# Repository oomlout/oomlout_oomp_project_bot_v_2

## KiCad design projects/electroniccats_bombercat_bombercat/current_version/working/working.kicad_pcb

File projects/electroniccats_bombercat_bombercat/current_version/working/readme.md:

# bombercat
 
## summary 
* id: electroniccats_bombercat_bombercat
* user: electroniccats
* name: bombercat
* board: bombercat
* repo: https://github.com/ElectronicCats/BomberCat
* src_file_repo_kicad_pcb: hardware/BomberCat.kicad_pcb
* src_file_repo_kicad_pcb_link: https://github.com/ElectronicCats/BomberCat/tree/main/hardware/BomberCat.kicad_pcb
* src_file_repo_kicad_sch: hardware/BomberCat.kicad_sch
* src_file_repo_kicad_sch_link: https://github.com/ElectronicCats/BomberCat/tree/main/hardware/BomberCat.kicad_sch

* src_file_repo_sch: 
* src_file_repo_sch_link: https://github.com/ElectronicCats/BomberCat/tree/main/
* full details link: https://github.com/oomlout/oomlout_oomp_project_bot_v_2/tree/main/projects/electroniccats_bombercat_bombercat/current_version/working

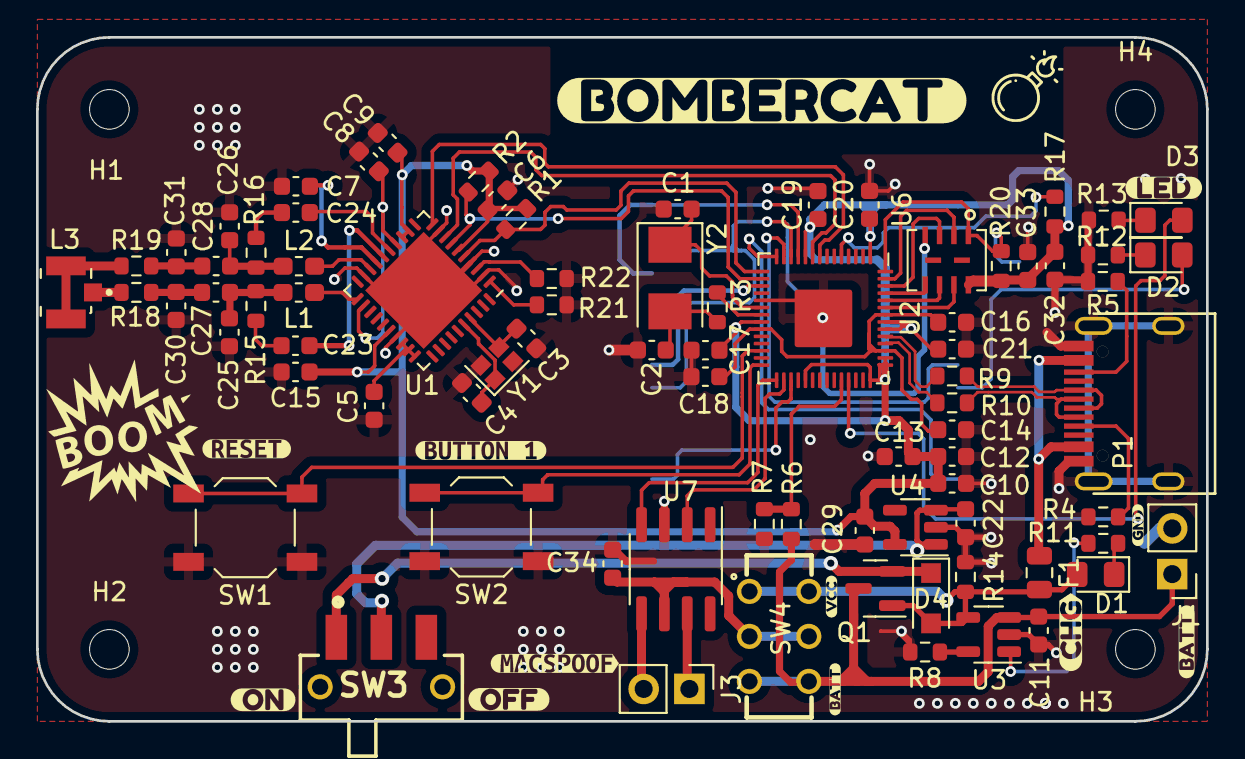
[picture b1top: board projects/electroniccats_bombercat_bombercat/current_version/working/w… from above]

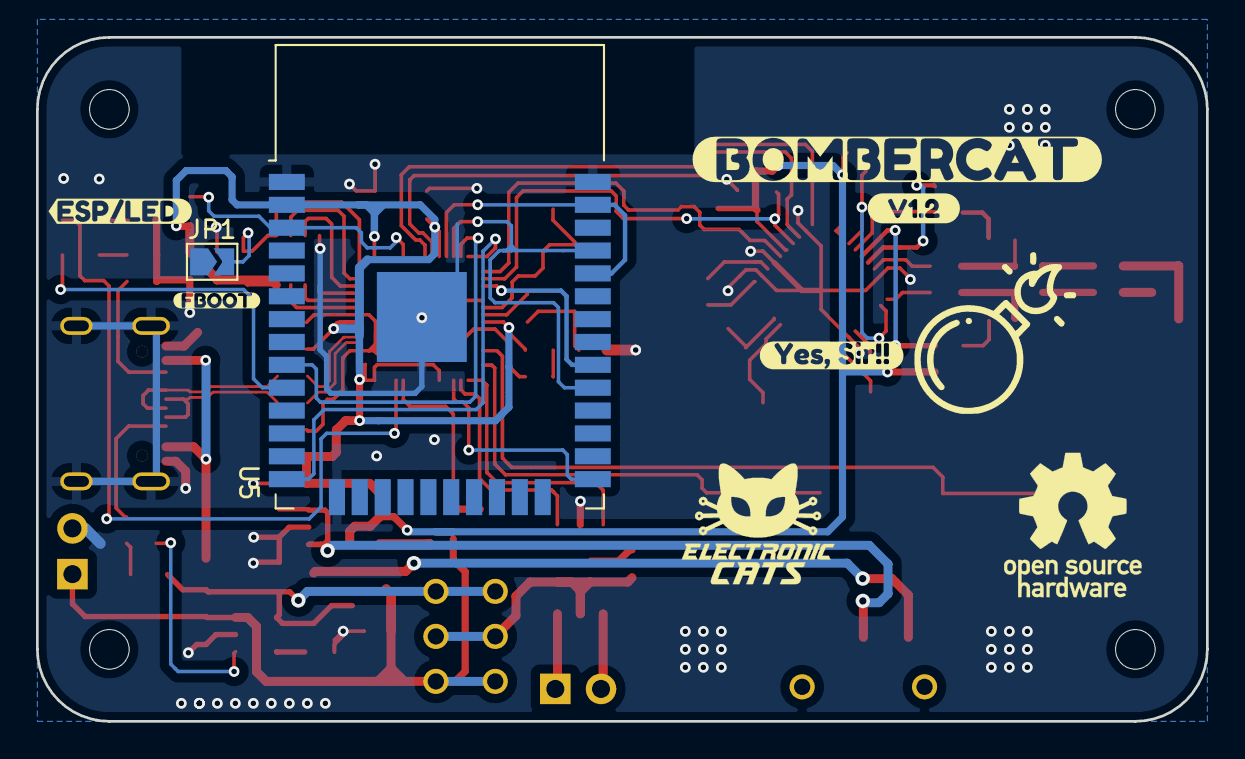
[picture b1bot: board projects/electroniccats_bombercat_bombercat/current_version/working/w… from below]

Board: 2 copper layers, 65.0 x 38.0 mm, 103 parts (7 on the bottom side), 68 nets.

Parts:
C1, C2: 27pF; C_0603_1608Metric
C3, C4: 10pF; C_0603_1608Metric
C5, C6, C8, C10, C14: 1uF; C_0603_1608Metric
C7, C9, C12, C13, C15, C16, C17, C18, C19, C20, C21, C32, C33: 100nF; C_0603_1608Metric
C11, C22, C29: 10uF; C_0603_1608Metric
C23, C24: 1nF/16V; C_0603_1608Metric
C25, C26: 680pF; C_0603_1608Metric
C27, C28: 100pF/50V; C_0603_1608Metric
C30, C31: 120pF; C_0603_1608Metric
C34: 10uf; C_0603_1608Metric
D1, D2, D3: LED; LED_0805_2012Metric_Pad1.15x1.40mm_HandSolder
D4: MBR120; D_SOD-123F
F1: 0.5A; Fuse_0805_2012Metric
H1, H2, H3, H4: MountingHole; MountingHole_2.2mm_M2
J1: Battery; PinHeader_1x02_P2.54mm_Vertical
J3: MAGSPOOF; PinHeader_1x02_P2.54mm_Vertical
JP1: BOOT; SolderJumper-2_P1.3mm_Open_TrianglePad1.0x1.5mm
L1, L2: 160nH; L_0603_1608Metric_Pad1.05x0.95mm_HandSolder
L3: L; MOLEX_1661
P1: USB_C_Plug_USB2.0; C393939
Q1: DMG3415U-7; SOT-23
R1, R2, R17, R20: 10K; R_0603_1608Metric
R3, R11, R12, R13: 1K; R_0603_1608Metric
R4, R5: 5k1; R_0603_1608Metric
R6, R7, R14, R21, R22: 100K; R_0603_1608Metric
R8: 2K; R_0603_1608Metric
R9, R10: 27; R_0603_1608Metric
R15, R16: 2k2; R_0603_1608Metric
R18, R19: 3.24R; R_0603_1608Metric
SW1: RESET; SW_SPST_TL3342
SW2: GPIO; SW_SPST_TL3342
SW3: ON; JS102011SAQN
SW4: SOURCE MAG; JS202011CQN
U1: PN7150B0HN_C11002E-PN7150B0HN_C11002E; QFN-40-1EP_6x6mm_P0.5mm_EP4.6x4.6mm
U2: RP2040; RP2040-QFN-56
U3: MCP73831-3-OT; SOT-23-5
U4: AP2112K-3.3; SOT-23-5
U5: ESP32-WROOM-32D; ESP32-WROOM-32
U6: W25Q16JV; W25Q16JVUUIQ
U7: TC4424; SOIC-8_3.9x4.9mm_P1.27mm
Y1: 27.12Mhz; Crystal_SMD_2016-4Pin_2.0x1.6mm
Y2: 12Mhz; Crystal_SMD_5032-2Pin_5.0x3.2mm
kibuzzard-62CC5B78, kibuzzard-62CC5B78#2: G***; kibuzzard-62CC5B78
kibuzzard-62CC5BEF: G***; kibuzzard-62CC5BEF
kibuzzard-62CC9A49: G***; kibuzzard-62CC9A49
kibuzzard-62CC57AB: G***; kibuzzard-62CC57AB
kibuzzard-62CC595D: G***; kibuzzard-62CC595D
kibuzzard-62CC5774: G***; kibuzzard-62CC5774
kibuzzard-62CC5787: G***; kibuzzard-62CC5787
kibuzzard-62CC5892: G***; kibuzzard-62CC5892
kibuzzard-62E1B2BF: G***; kibuzzard-62E1B2BF
kibuzzard-62E1B24A: G***; kibuzzard-62E1B24A
kibuzzard-62E1B288: G***; kibuzzard-62E1B288
kibuzzard-62E1B296: G***; kibuzzard-62E1B296
kibuzzard-62E41048: G***; kibuzzard-62E41048
kibuzzard-62EEB073: G***; kibuzzard-62EEB073
kibuzzard-62EEB113: G***; kibuzzard-62EEB113
kibuzzard-64382690: G***; kibuzzard-64382690

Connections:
+1V2: C14.1, C16.1, C18.1, U2.23 (DVDD), U2.45 (VREG_VOUT), U2.50 (DVDD)
+3V3: C6.1, C9.1, C10.1, C12.1, C13.1, C15.1, C17.1, C19.1, C20.1, C21.1, C29.1, C32.1, C33.1, R1.1, R2.1, R17.1, R20.1, U1.6 (VDD(PAD)), U1.12 (VBAT2), U1.13 (VBAT1), U1.26 (VBAT), U2.1 (IOVDD), U2.10 (IOVDD), U2.22 (IOVDD), U2.33 (IOVDD), U2.42 (IOVDD), U2.43 (ADC_AVDD), U2.44 (VREG_IN), U2.48 (USB_VDD), U2.49 (IOVDD), U4.5 (VOUT), U5.2 (VDD), U6.8 (VCC)
+BATT: C11.1, J1.1, Q1.3 (D), R6.1, SW4.3 (C), U3.3 (VBAT)
/ACK_CTS: U2.13 (GPIO10), U5.9 (IO33)
/ADR0: R21.1, U1.1 (I2CADR0)
/ADR1: R22.1, U1.3 (I2CADR1)
/B_ADC: R6.2, R7.1, U2.38 (GPIO26_ADC0)
/CIPO_TX: U2.11 (GPIO8), U5.34 (RXD0/IO3), U5.37 (IO23)
/COPI_RTS: U2.14 (GPIO11), U5.14 (IO12)
/CS_RX: U2.12 (GPIO9), U5.29 (IO5), U5.35 (TXD0/IO1)
/D+: P1.A6 (D+), R9.1
/D-: P1.A7 (D-), R10.1
/ESP_GPIO0: U2.31 (GPIO20), U5.25 (IO0)
/ESP_LED: D2.2 (A), U5.10 (IO25)
/ESP_RESET: R17.2, U2.5 (GPIO3), U5.3 (EN)
/GPIO1: SW2.2, U2.28 (GPIO17)
/IN_A: U2.30 (GPIO19), U7.2 (IN_A)
/IN_B: U2.29 (GPIO18), U7.4 (IN_B)
/IRQ: U1.8 (IRQ), U2.9 (GPIO7)
/LED1: D3.2 (A), U2.39 (GPIO27_ADC1)
/OUTA: J3.1, U7.7 (OUT_A)
/OUTB: J3.2, U7.5 (OUT_B)
/QSPI_CS: JP1.2 (B), R20.2, U2.56 (QSPI_SS), U6.1 (~CS)
/QSPI_DATA0: U2.53 (QSPI_SD0), U6.5 (DI(IO0))
/QSPI_DATA1: U2.55 (QSPI_SD1), U6.2 (DO(IO1))
/QSPI_DATA2: U2.54 (QSPI_SD2), U6.3 (IO2)
/QSPI_DATA3: U2.51 (QSPI_SD3), U6.7 (IO3)
/QSPI_SCK: U2.52 (QSPI_SCLK), U6.6 (CLK)
/RD+: R9.2, U2.47 (USB_DP)
/RD-: R10.2, U2.46 (USB_DM)
/RST: SW1.2, U2.26 (RUN)
/RXN: C24.2, U1.15 (RXN)
/RXP: C23.2, U1.16 (RXP)
/SCK: U2.17 (GPIO14), U5.30 (IO18)
/SCL: R2.2, U1.7 (I2CSCL), U2.16 (GPIO13)
/SDA: R1.2, U1.5 (I2CSDA), U2.15 (GPIO12)
/TX1: L1.1, U1.21 (TX1)
/TX2: L2.2, U1.18 (TX2)
/VEN: U1.10 (VEN), U2.8 (GPIO6)
GND: C1.2, C2.2, C3.2, C4.2, C5.2, C6.2, C7.2, C8.2, C9.2, C10.2, C11.2, C12.2, C13.2, C14.2, C15.2, C16.2, C17.2, C18.2, C19.2, C20.2, C21.2, C22.2, C25.2, C26.1, C29.2, C30.2, C31.1, C32.2, C33.2, C34.2, J1.2, JP1.1 (A), P1.A1 (GND), R4.1, R5.1, R7.2, R8.2, R12.2, R13.2, R14.2, R21.2, R22.2, SW1.1, SW2.1, U1.2 (VSS), U1.4 (VSS(PAD)), U1.9 (VSS), U1.19 (VSS(TX)), U1.27 (VSS), U1.41 (VSS), U2.19 (TESTEN), U2.57 (GND), U3.2 (VSS), U4.2 (GND), U5.1 (GND), U5.15 (GND), U5.38 (GND), U5.39 (GND), U6.4 (GND), U7.3 (GND), Y1.2, Y1.4
unnamed: C1.1, U2.20 (XIN), Y2.1
unnamed: C2.1, R3.1, Y2.2
unnamed: C3.1, U1.37 (NFC_CLK_XTAL2), Y1.3
unnamed: C4.1, U1.36 (NFC_CLK_XTAL1), Y1.1
unnamed: C5.1, U1.28 (VDDA), U1.29 (VDD), U1.30 (VDDD)
unnamed: C7.1, U1.17 (VDD(MID))
unnamed: C8.1, U1.14 (VDD(TX)), U1.22 (VDD(TX_IN))
unnamed: C22.1, SW3.2 (B), U4.1 (VIN), U4.3 (EN)
unnamed: C23.1, R15.1
unnamed: C24.1, R16.2
unnamed: C25.1, C27.2, L1.2, R15.2
unnamed: C26.2, C28.2, L2.1, R16.1
unnamed: C27.1, C30.1, R18.2
unnamed: C28.1, C31.2, R19.2
unnamed: C34.1, SW4.2 (B), U7.6 (VDD)
unnamed: D1.1 (K), R11.2
unnamed: D2.1 (K), R12.1
unnamed: D3.1 (K), R13.1
unnamed: D4.1 (K), Q1.2 (S), SW3.1 (A)
unnamed: F1.1, P1.A4 (VBUS)
unnamed: L3.1, R18.1
unnamed: L3.2, R19.1
unnamed: P1.A5 (CC), R4.2
unnamed: P1.B5 (VCONN), R5.2
unnamed: R3.2, U2.21 (XOUT)
unnamed: R8.1, U3.5 (PROG)
unnamed: R11.1, U3.1 (STAT)
VBUS: D1.2 (A), D4.2 (A), F1.2, Q1.1 (G), R14.1, SW4.1 (A), U3.4 (VDD)

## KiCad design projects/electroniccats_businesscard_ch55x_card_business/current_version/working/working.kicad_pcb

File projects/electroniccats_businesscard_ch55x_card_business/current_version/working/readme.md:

# businesscard_ch55x
 
## summary 
* id: electroniccats_businesscard_ch55x_card_business
* user: electroniccats
* name: businesscard_ch55x
* board: card_business
* repo: https://github.com/ElectronicCats/businessCard-ch55x
* src_file_repo_kicad_pcb: hardware/card_business.kicad_pcb
* src_file_repo_kicad_pcb_link: https://github.com/ElectronicCats/businessCard-ch55x/tree/main/hardware/card_business.kicad_pcb

* src_file_repo_sch: hardware/card_business.sch
* src_file_repo_sch_link: https://github.com/ElectronicCats/businessCard-ch55x/tree/main/hardware/card_business.sch
* full details link: https://github.com/oomlout/oomlout_oomp_project_bot_v_2/tree/main/projects/electroniccats_businesscard_ch55x_card_business/current_version/working

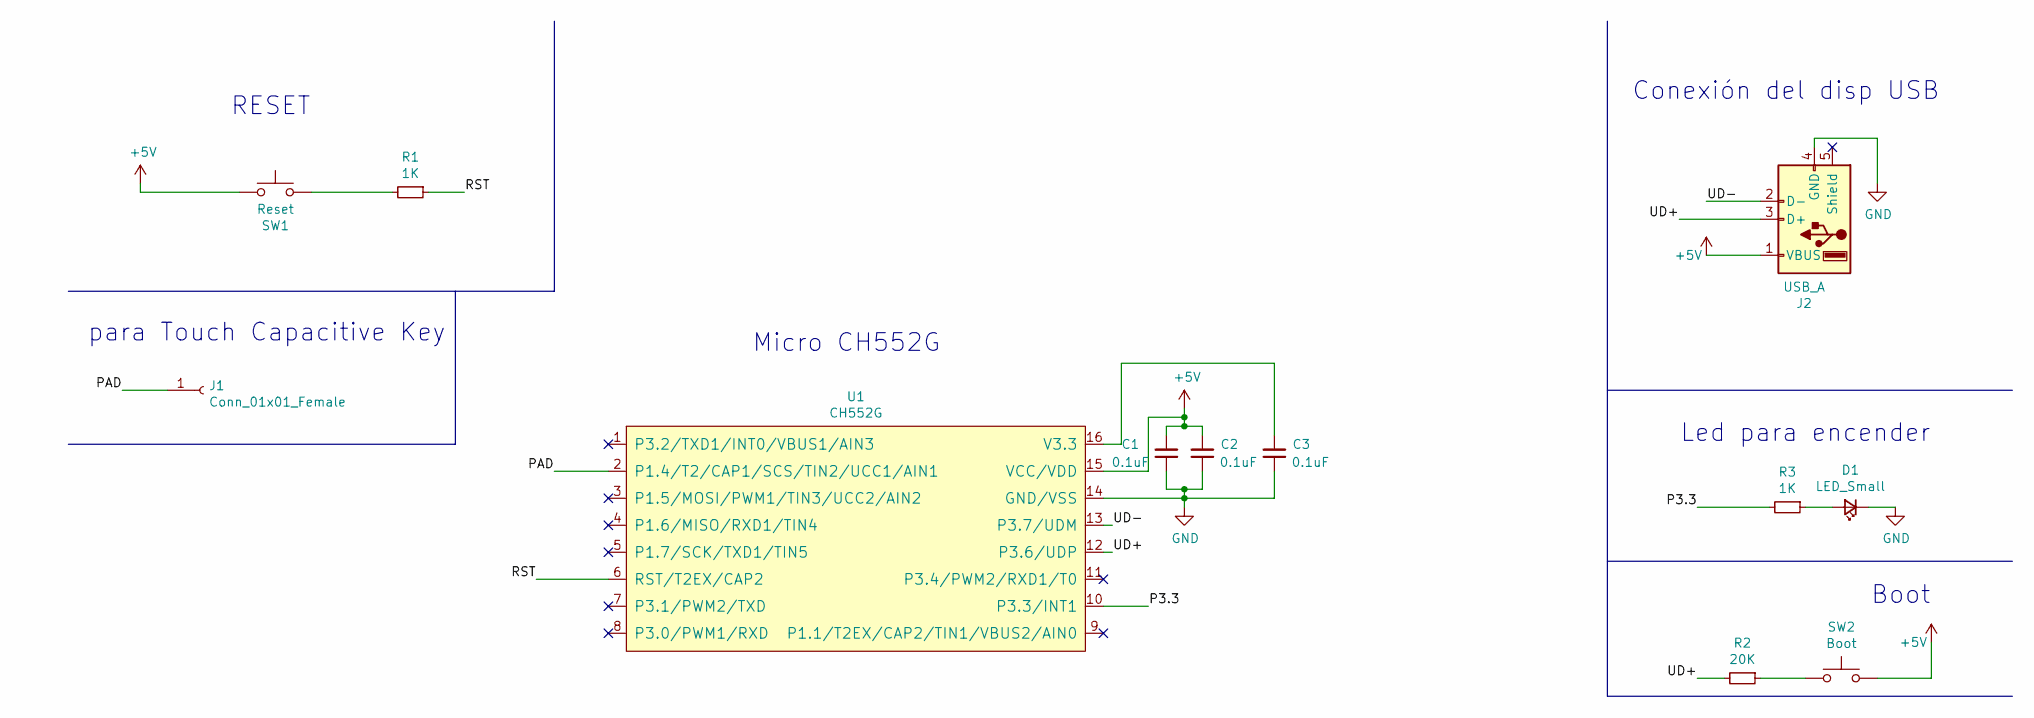
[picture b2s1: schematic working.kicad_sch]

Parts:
C1, C2, C3: 0.1uF; C_0805_2012Metric
D1: LED_Small; LED_0805_2012Metric
J1: Conn_01x01_Female; TestPoint_Pad_D4.0mm
J2: USB_A; usb-PCB
R1, R3: 1K; R_0805_2012Metric
R2: 20K; R_0805_2012Metric
SW1: Reset; SW_SPST_TL3342
SW2: Boot; SW_SPST_TL3342
U1: CH552G; SOP-16_4.55x10.3mm_P1.27mm

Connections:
+5V: C1.2, C2.2, J2.1 (VBUS), SW1.1, SW2.2, U1.15 (VCC/VDD)
/P3.3: R3.2, U1.10 (P3.3/INT1)
/PAD: J1.1, U1.2 (P1.4/T2/CAP1/SCS/TIN2/UCC1/AIN1)
/RST: R1.1, U1.6 (RST/T2EX/CAP2)
/UD+: J2.3 (D+), R2.2, U1.12 (P3.6/UDP)
/UD-: J2.2 (D-), U1.13 (P3.7/UDM)
GND: C1.1, C2.1, C3.1, D1.1 (K), J2.4 (GND), U1.14 (GND/VSS)
unnamed: C3.2, U1.16 (V3.3)
unnamed: D1.2 (A), R3.1
unnamed: R1.2, SW1.2
unnamed: R2.1, SW2.1

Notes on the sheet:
Boot
Led para encender
RESET
Conexión del disp USB
Micro CH552G
para Touch Capacitive Key

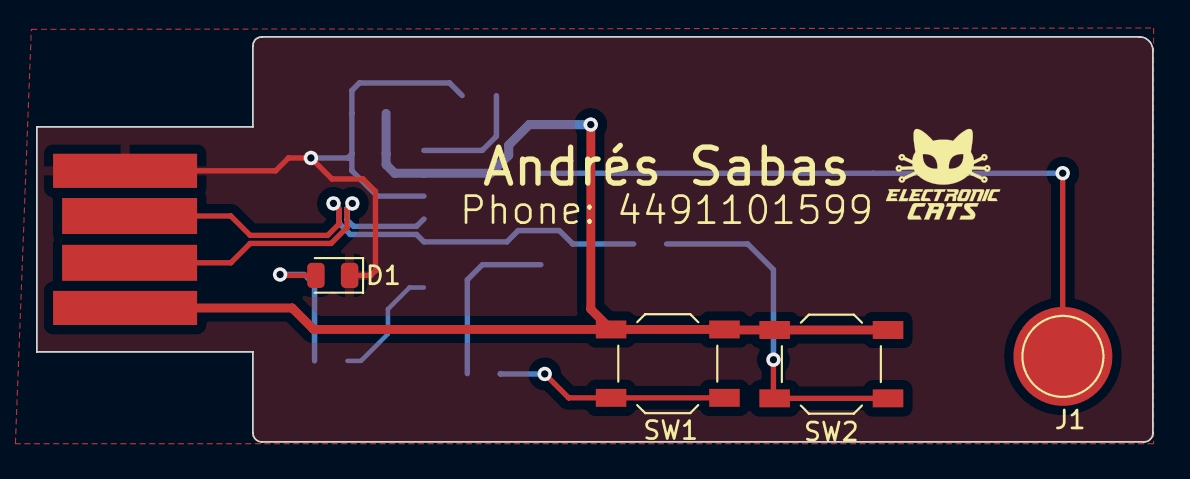
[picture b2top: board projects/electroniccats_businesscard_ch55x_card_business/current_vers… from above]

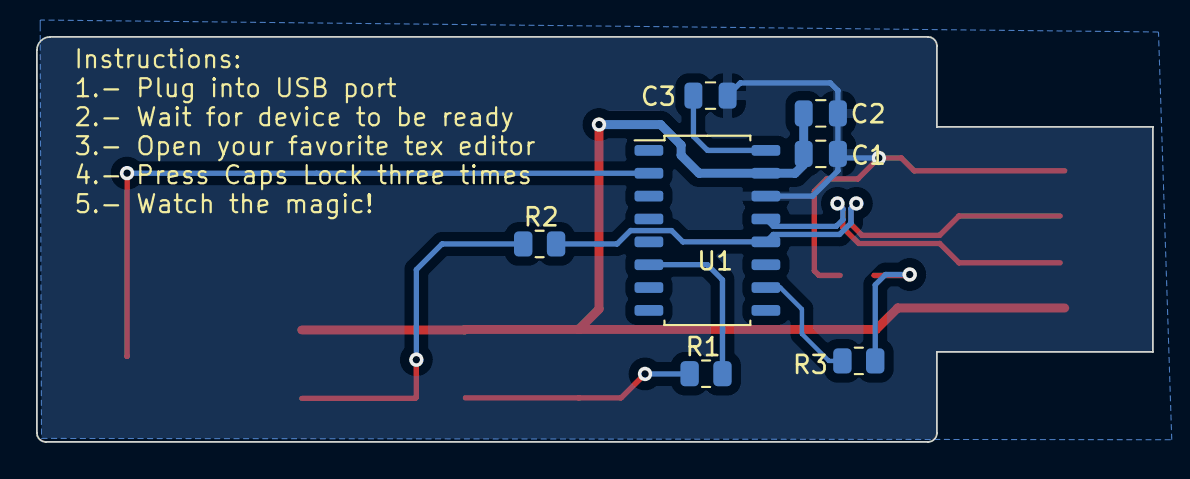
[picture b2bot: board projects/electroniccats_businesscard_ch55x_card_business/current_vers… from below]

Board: 2 copper layers, 62.0 x 22.5 mm, 12 parts (7 on the bottom side), 11 nets.

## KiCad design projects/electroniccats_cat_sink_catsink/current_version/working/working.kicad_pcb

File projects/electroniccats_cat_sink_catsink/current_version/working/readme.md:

# cat_sink
 
## summary 
* id: electroniccats_cat_sink_catsink
* user: electroniccats
* name: cat_sink
* board: catsink
* repo: https://github.com/ElectronicCats/Cat-Sink
* src_file_repo_kicad_pcb: Hw/CatSink/CatSink.kicad_pcb
* src_file_repo_kicad_pcb_link: https://github.com/ElectronicCats/Cat-Sink/tree/main/Hw/CatSink/CatSink.kicad_pcb
* src_file_repo_kicad_sch: Hw/CatSink/CatSink.kicad_sch
* src_file_repo_kicad_sch_link: https://github.com/ElectronicCats/Cat-Sink/tree/main/Hw/CatSink/CatSink.kicad_sch

* src_file_repo_sch: Hw/CatSink/CatSink.sch
* src_file_repo_sch_link: https://github.com/ElectronicCats/Cat-Sink/tree/main/Hw/CatSink/CatSink.sch
* full details link: https://github.com/oomlout/oomlout_oomp_project_bot_v_2/tree/main/projects/electroniccats_cat_sink_catsink/current_version/working

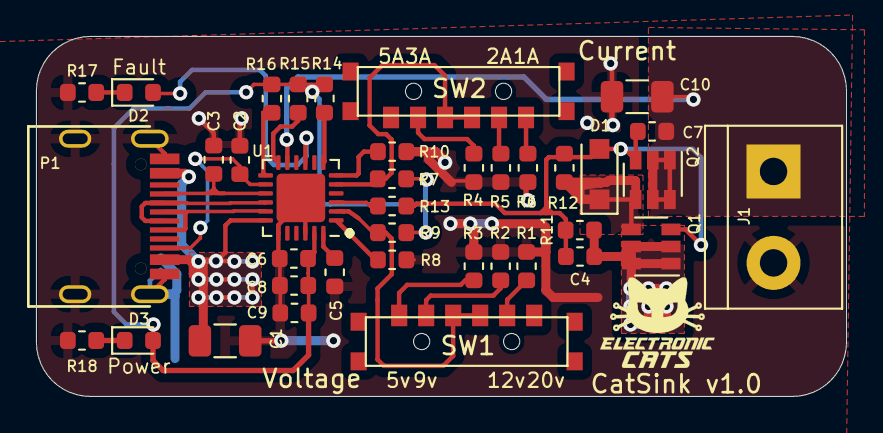
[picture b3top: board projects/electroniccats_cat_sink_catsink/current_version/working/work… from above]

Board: 2 copper layers, 45.0 x 20.0 mm, 38 parts (0 on the bottom side), 28 nets.

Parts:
C1, C10: 3.3uF; C_1206_3216Metric
C2, C3: 390pF; C_0603_1608Metric
C4, C5, C6, C7: 1uF; C_0603_1608Metric
C8, C9: 0.1uF; C_0603_1608Metric
D1: NZH10C; D_SOD-123F
D2: Fault; LED_0603_1608Metric
D3: Power; LED_0603_1608Metric
J1: Vout; TerminalBlock_bornier-2_P5.08mm
P1: USB_C_Plug_USB2.0; C393939
Q1, Q2: SI3421DV; SOT-23-6
R1, R5: 2.4K; R_0603_1608Metric
R2, R6, R13, R18: 1K; R_0603_1608Metric
R3: 0R; R_0603_1608Metric
R4, R7, R8, R9, R10: 5.1K; R_0603_1608Metric
R11, R14, R15, R16, R17: 10K; R_0603_1608Metric
R12: 50K; R_0603_1608Metric
SW1: Voltage; K3-1410S-E1
SW2: Current; K3-1410S-E1
U1: CYPD3177-24LQXI; QFN-24-1EP_4x4mm_P0.5mm_EP2.7x2.7mm

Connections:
+3V3: C6.1, C8.1, C9.1, D3.2, R7.1, R9.1, R14.1, R15.1, R16.1, U1.23
+VSW: C7.1, C10.1, J1.1, Q2.1, Q2.2, Q2.5, Q2.6, U1.11
/1A: R6.1, SW2.1
/2A: R5.1, SW2.2
/3A: R4.1, SW2.5
/5v: R3.1, SW1.1
/9v: R2.1, SW1.2
/12v: R1.1, SW1.5
/CC1: C3.1, P1.A5, U1.15
/CC2: C2.1, P1.B5, U1.14
/D+: P1.A6, U1.17
/D-: P1.A7, U1.16
/Fault: D2.2, U1.9
/Icoarse: R7.2, SW2.3, SW2.4, U1.5
/Vmax: R9.2, SW1.3, SW1.4, U1.2
GND: C1.2, C2.2, C3.2, C5.2, C6.2, C8.2, C9.2, C10.2, J1.2, P1.A1, P1.S1, R1.2, R2.2, R3.2, R4.2, R5.2, R6.2, R8.2, R10.2, R17.2, R18.2, U1.19, U1.22, U1.25
unnamed: C4.2, C7.2, D1.2, Q1.3, Q2.3, R11.2, R12.2, R13.1
unnamed: C5.1, U1.24
unnamed: D1.1, Q1.4, Q2.4, R12.1
unnamed: D2.1, R17.1
unnamed: D3.1, R18.1
unnamed: R8.1, U1.1
unnamed: R10.1, U1.6
unnamed: R13.2, U1.3
unnamed: R14.2, U1.7
unnamed: R15.2, U1.12
unnamed: R16.2, U1.13
VBUS: C1.1, C4.1, P1.A4, Q1.1, Q1.2, Q1.5, Q1.6, R11.1, U1.18

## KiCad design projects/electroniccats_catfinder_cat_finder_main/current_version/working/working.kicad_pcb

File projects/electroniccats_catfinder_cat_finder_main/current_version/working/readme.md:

# catfinder
 
## summary 
* id: electroniccats_catfinder_cat_finder_main
* user: electroniccats
* name: catfinder
* board: cat_finder_main
* repo: https://github.com/ElectronicCats/CatFinder
* src_file_repo_kicad_pcb: Hardware/cat_finder_main/cat_finder_main.kicad_pcb
* src_file_repo_kicad_pcb_link: https://github.com/ElectronicCats/CatFinder/tree/master/Hardware/cat_finder_main/cat_finder_main.kicad_pcb

* src_file_repo_sch: Hardware/cat_finder_main/cat_finder_main.sch
* src_file_repo_sch_link: https://github.com/ElectronicCats/CatFinder/tree/master/Hardware/cat_finder_main/cat_finder_main.sch
* full details link: https://github.com/oomlout/oomlout_oomp_project_bot_v_2/tree/main/projects/electroniccats_catfinder_cat_finder_main/current_version/working

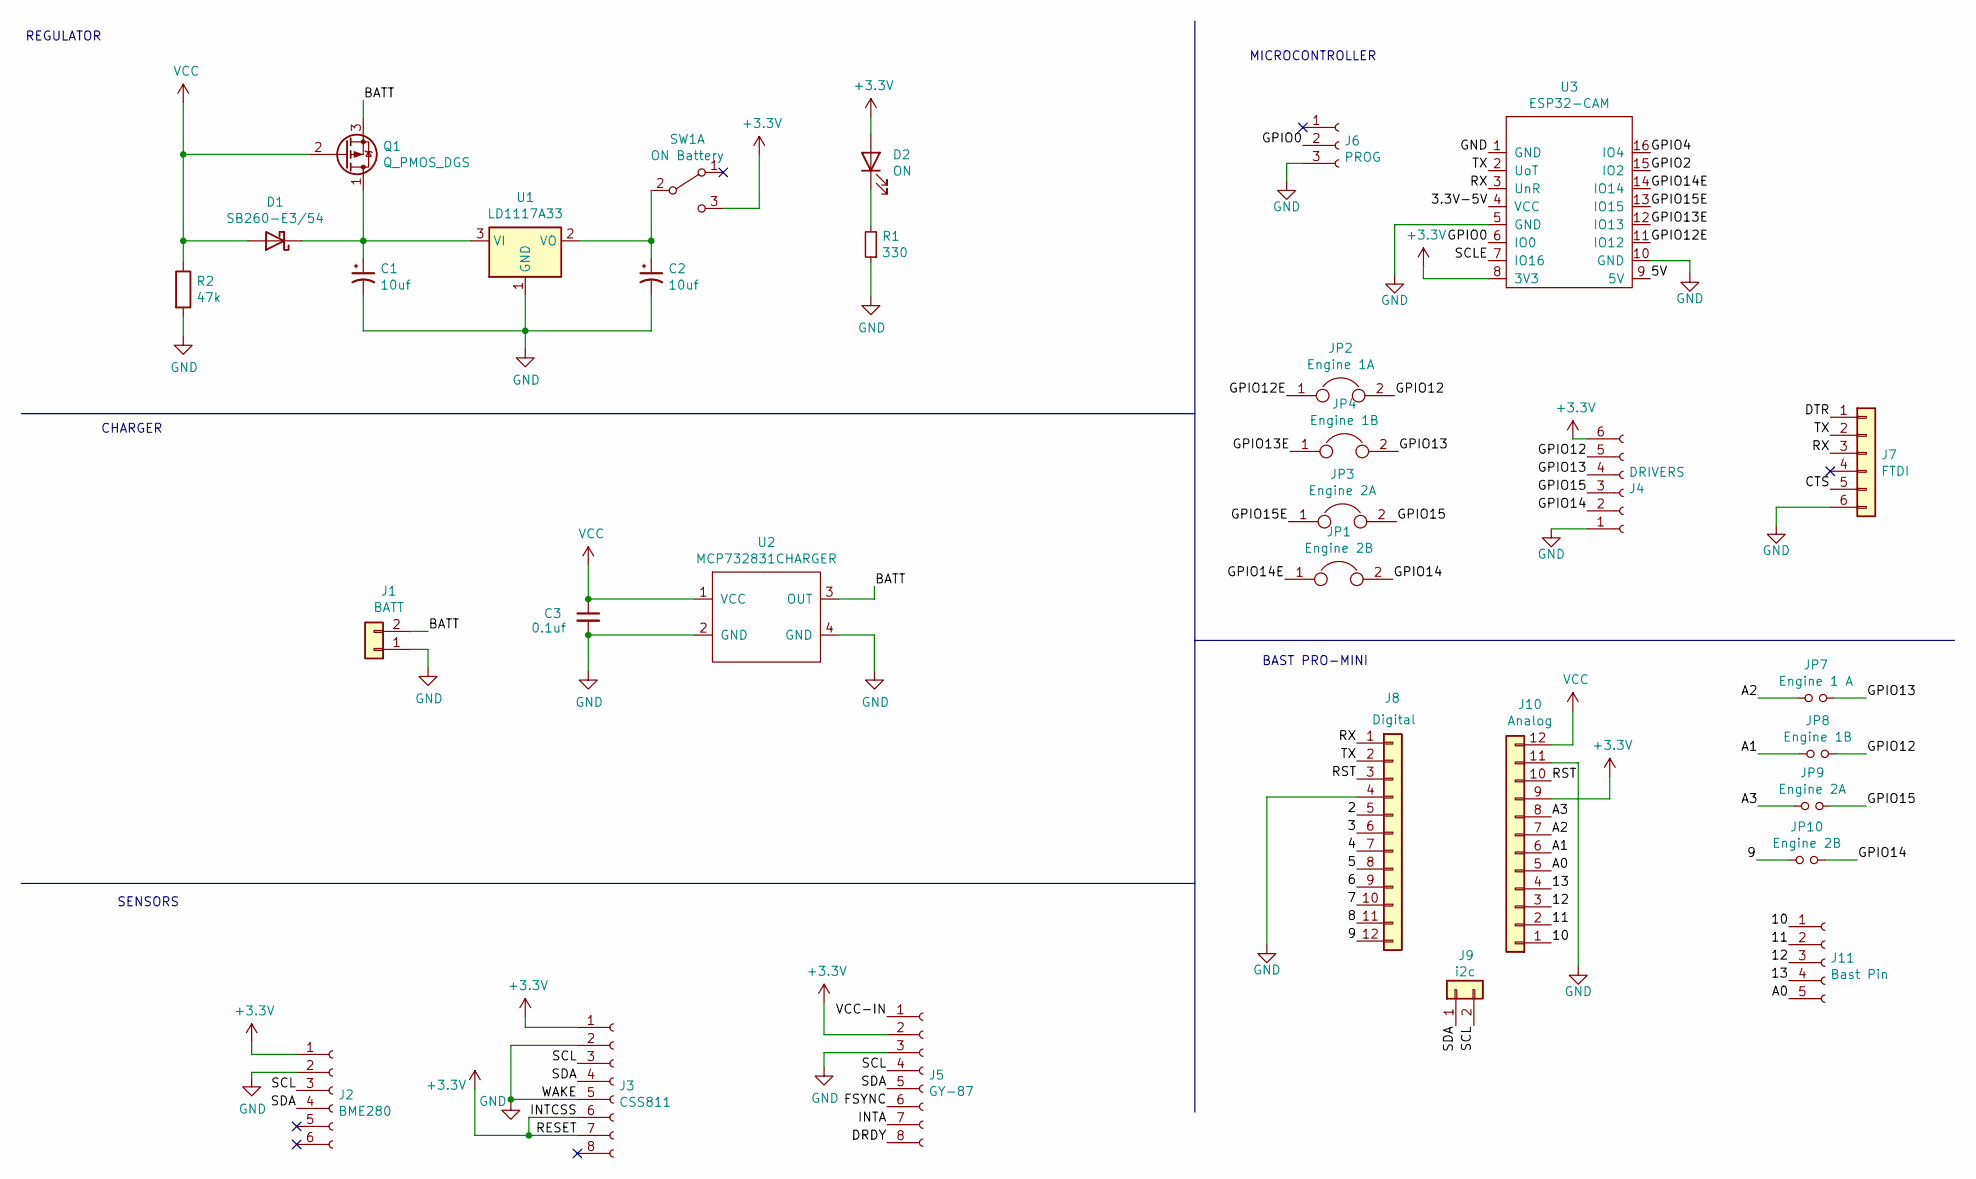
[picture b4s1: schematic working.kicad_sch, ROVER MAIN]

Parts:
C1, C2: 10uf; CP_Radial_D5.0mm_P2.00mm
C3: 0.1uf; C_Disc_D5.0mm_W2.5mm_P5.00mm
D1: SB260-E3/54; D_A-405_P7.62mm_Horizontal
D2: ON; LED_D5.0mm
J1: BATT; TerminalBlock_bornier-2_P5.08mm
J2: BME280; PinHeader_1x06_P2.54mm_Vertical
J3: CSS811; PinHeader_1x08_P2.54mm_Vertical
J4: DRIVERS; PinHeader_1x06_P2.54mm_Vertical
J5: GY-87; PinHeader_1x08_P2.54mm_Vertical
J6: PROG; PinHeader_1x03_P2.54mm_Vertical
J7: FTDI; PinHeader_1x06_P2.54mm_Vertical
J8: Digital; PinHeader_1x12_P2.54mm_Vertical
J9: i2c; PinHeader_1x02_P2.54mm_Vertical
J10: Analog; PinHeader_1x12_P2.54mm_Vertical
J11: Bast Pin; PinSocket_1x05_P2.54mm_Vertical
JP1: Engine 2B; SolderJumper-2_P1.3mm_Bridged_RoundedPad1.0x1.5mm
JP2: Engine 1A; SolderJumper-2_P1.3mm_Bridged_RoundedPad1.0x1.5mm
JP3: Engine 2A; SolderJumper-2_P1.3mm_Bridged_RoundedPad1.0x1.5mm
JP4: Engine 1B; SolderJumper-2_P1.3mm_Bridged_RoundedPad1.0x1.5mm
JP7: Engine 1 A; SolderJumper-2_P1.3mm_Open_RoundedPad1.0x1.5mm
JP8: Engine 1B; SolderJumper-2_P1.3mm_Open_RoundedPad1.0x1.5mm
JP9: Engine 2A; SolderJumper-2_P1.3mm_Open_RoundedPad1.0x1.5mm
JP10: Engine 2B; SolderJumper-2_P1.3mm_Open_RoundedPad1.0x1.5mm
Q1: Q_PMOS_DGS; TO-92_Inline
R1: 330; R_Axial_DIN0207_L6.3mm_D2.5mm_P10.16mm_Horizontal
R2: 47k; R_Axial_DIN0207_L6.3mm_D2.5mm_P10.16mm_Horizontal
SW1: ON Battery; SW_1825116-1
U1: LD1117A33; TO-220-3_Vertical
U2: MCP732831CHARGER; charger_EC_3.3V_battery
U3: ESP32-CAM

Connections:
+3V3: D2.2 (A), J2.1, J3.1, J3.6, J3.7, J4.6, J5.2, J10.9, SW1.3 (C), U3.8 (3V3)
/2: J8.5
/3: J8.6
/3.3V-5V: U3.4 (VCC)
/4: J8.7
/5: J8.8
/5V: U3.9 (5V)
/6: J8.9
/7: J8.10
/8: J8.11
/9: J8.12, JP10.1
/10: J10.1, J11.1
/11: J10.2, J11.2
/12: J10.3, J11.3
/13: J10.4, J11.4
/A0: J10.5, J11.5
/A1: J10.6, JP8.1
/A2: J10.7, JP7.1
/A3: J10.8, JP9.1
/BATT: J1.2, Q1.3 (S), U2.3 (OUT)
/CTS: J7.5
/DRDY: J5.8
/DTR: J7.1
/FSYNC: J5.6
/GPIO0: J6.2, U3.6 (IO0)
/GPIO2: U3.15 (IO2)
/GPIO4: U3.16 (IO4)
/GPIO12: J4.5, JP2.2, JP8.2
/GPIO12E: JP2.1, U3.11 (IO12)
/GPIO13: J4.4, JP4.2, JP7.2
/GPIO13E: JP4.1, U3.12 (IO13)
/GPIO14: J4.2, JP1.2, JP10.2
/GPIO14E: JP1.1, U3.14 (IO14)
/GPIO15: J4.3, JP3.2, JP9.2
/GPIO15E: JP3.1, U3.13 (IO15)
/INTA: J5.7
/RST: J8.3, J10.10
/RX: J7.3, J8.1, U3.3 (UnR)
/SCL: J2.3, J3.3, J5.4, J9.2
/SCLE: U3.7 (IO16)
/SDA: J2.4, J3.4, J5.5, J9.1
/TX: J7.2, J8.2, U3.2 (UoT)
/VCC-IN: J5.1
GND: C1.2, C2.2, C3.2, J1.1, J2.2, J3.2, J3.5, J4.1, J5.3, J6.3, J7.6, J8.4, J10.11, R1.1, R2.2, U1.1 (GND), U2.2 (GND), U2.4 (GND), U3.1 (GND), U3.5 (GND), U3.10 (GND)
unnamed: C1.1, D1.1 (K), Q1.1 (D), U1.3 (VI)
unnamed: C2.1, SW1.2 (B), U1.2 (VO)
unnamed: D2.1 (K), R1.2
VCC: C3.1, D1.2 (A), J10.12, Q1.2 (G), R2.1, U2.1 (VCC)

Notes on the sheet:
CHARGER
BAST PRO-MINI
REGULATOR
MICROCONTROLLER
SENSORS

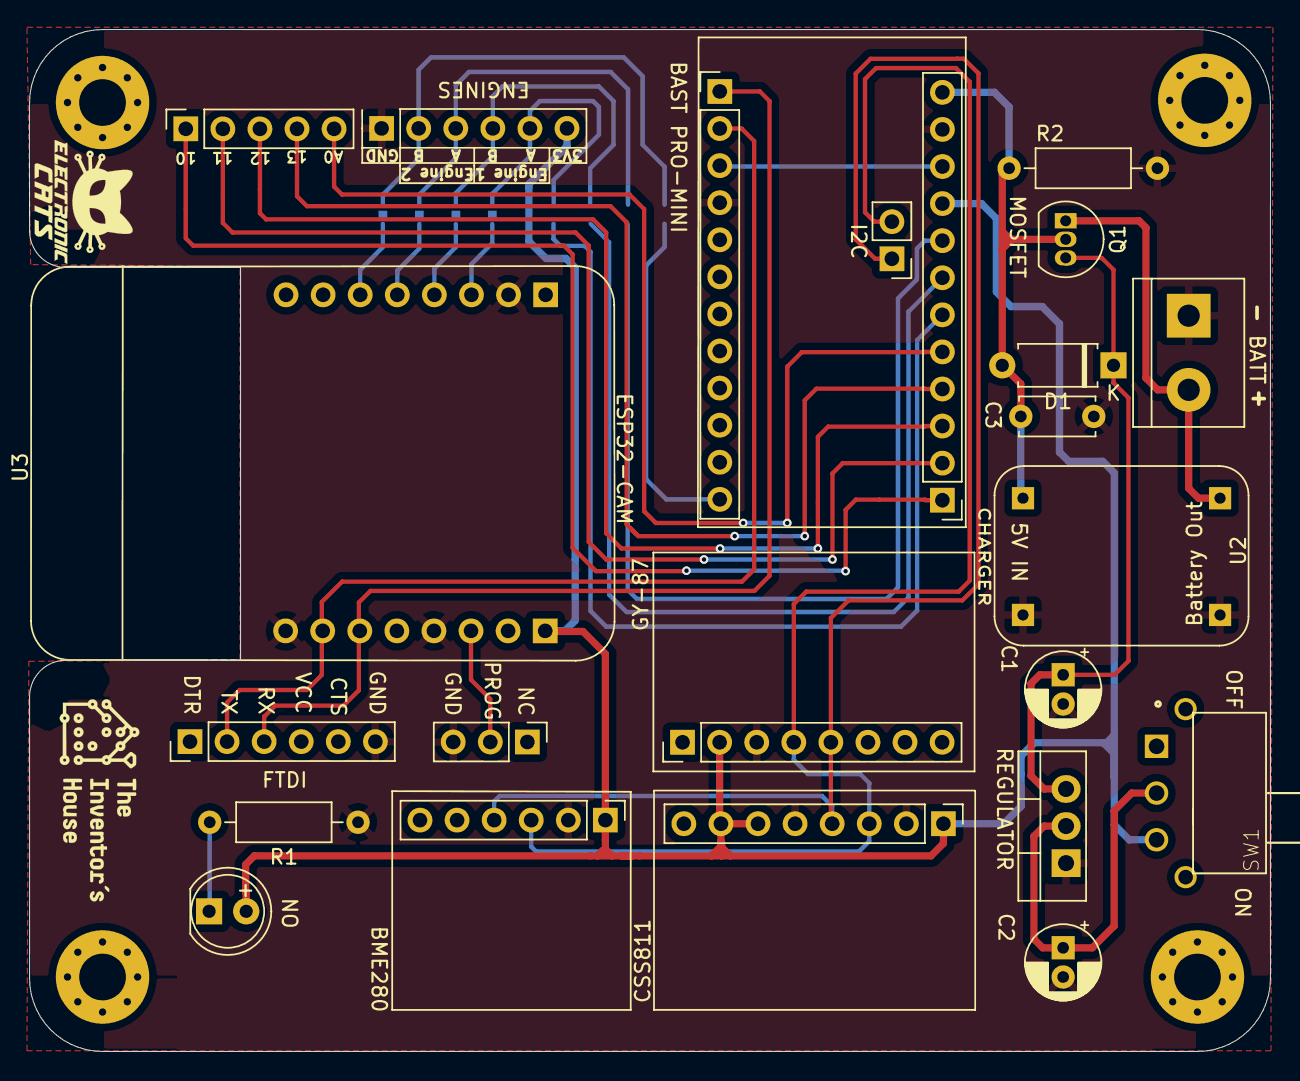
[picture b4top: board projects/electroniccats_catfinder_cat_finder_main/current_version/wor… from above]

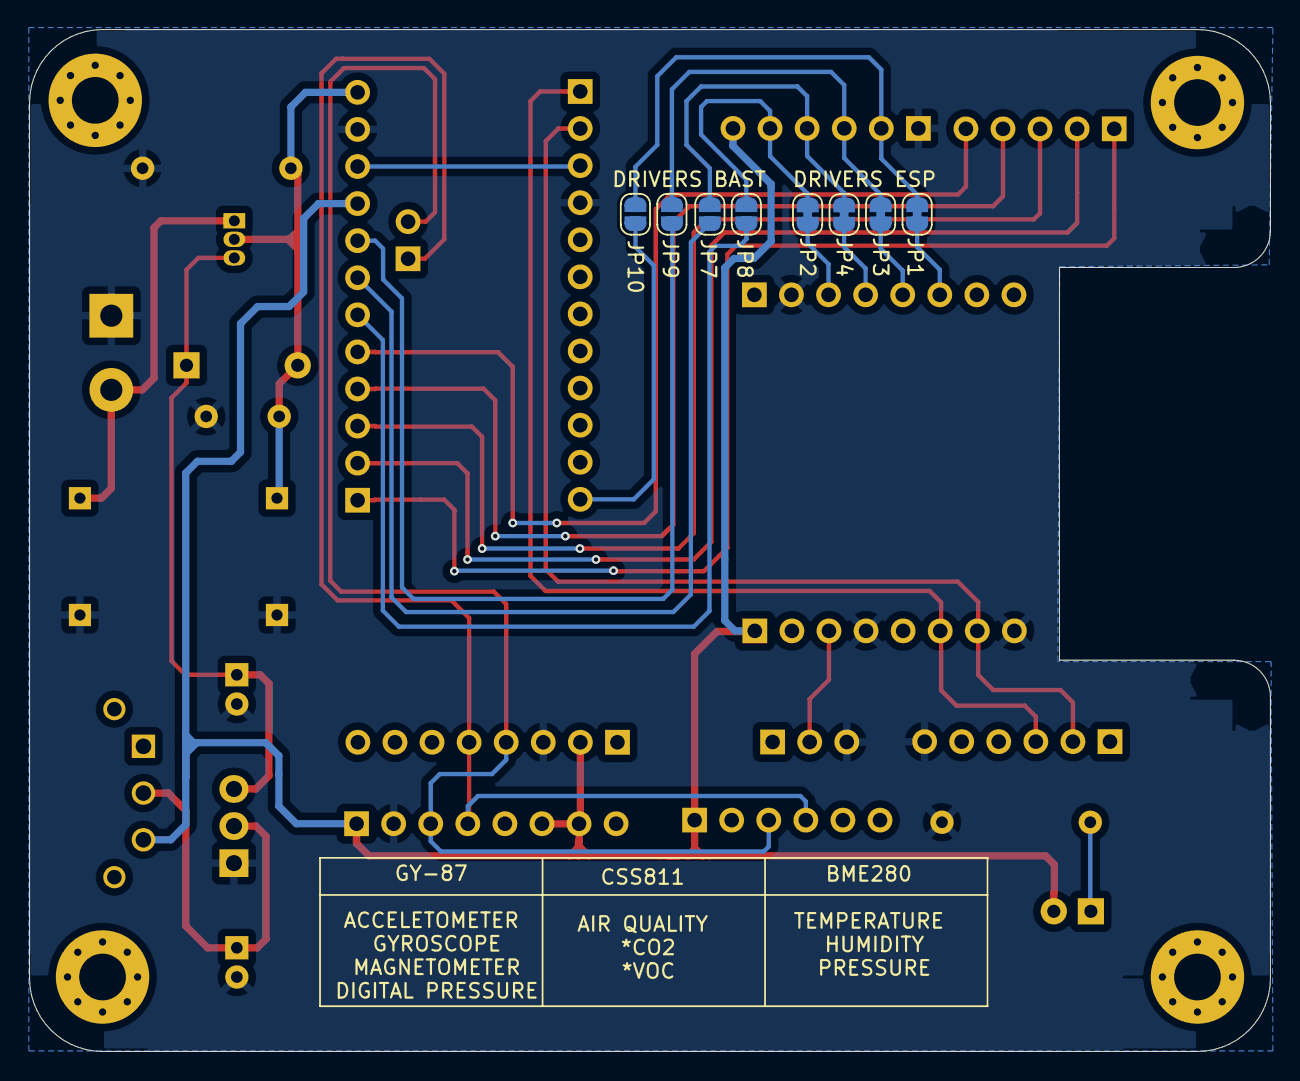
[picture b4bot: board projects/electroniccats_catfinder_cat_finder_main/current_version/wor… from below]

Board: 2 copper layers, 85.0 x 70.0 mm, 31 parts (8 on the bottom side), 30 nets.

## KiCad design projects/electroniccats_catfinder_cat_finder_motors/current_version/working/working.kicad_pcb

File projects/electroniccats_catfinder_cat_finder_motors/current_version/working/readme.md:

# catfinder
 
## summary 
* id: electroniccats_catfinder_cat_finder_motors
* user: electroniccats
* name: catfinder
* board: cat_finder_motors
* repo: https://github.com/ElectronicCats/CatFinder
* src_file_repo_kicad_pcb: Hardware/cat_finder_motors/cat_finder_motors.kicad_pcb
* src_file_repo_kicad_pcb_link: https://github.com/ElectronicCats/CatFinder/tree/master/Hardware/cat_finder_motors/cat_finder_motors.kicad_pcb

* src_file_repo_sch: Hardware/cat_finder_motors/cat_finder_motors.sch
* src_file_repo_sch_link: https://github.com/ElectronicCats/CatFinder/tree/master/Hardware/cat_finder_motors/cat_finder_motors.sch
* full details link: https://github.com/oomlout/oomlout_oomp_project_bot_v_2/tree/main/projects/electroniccats_catfinder_cat_finder_motors/current_version/working

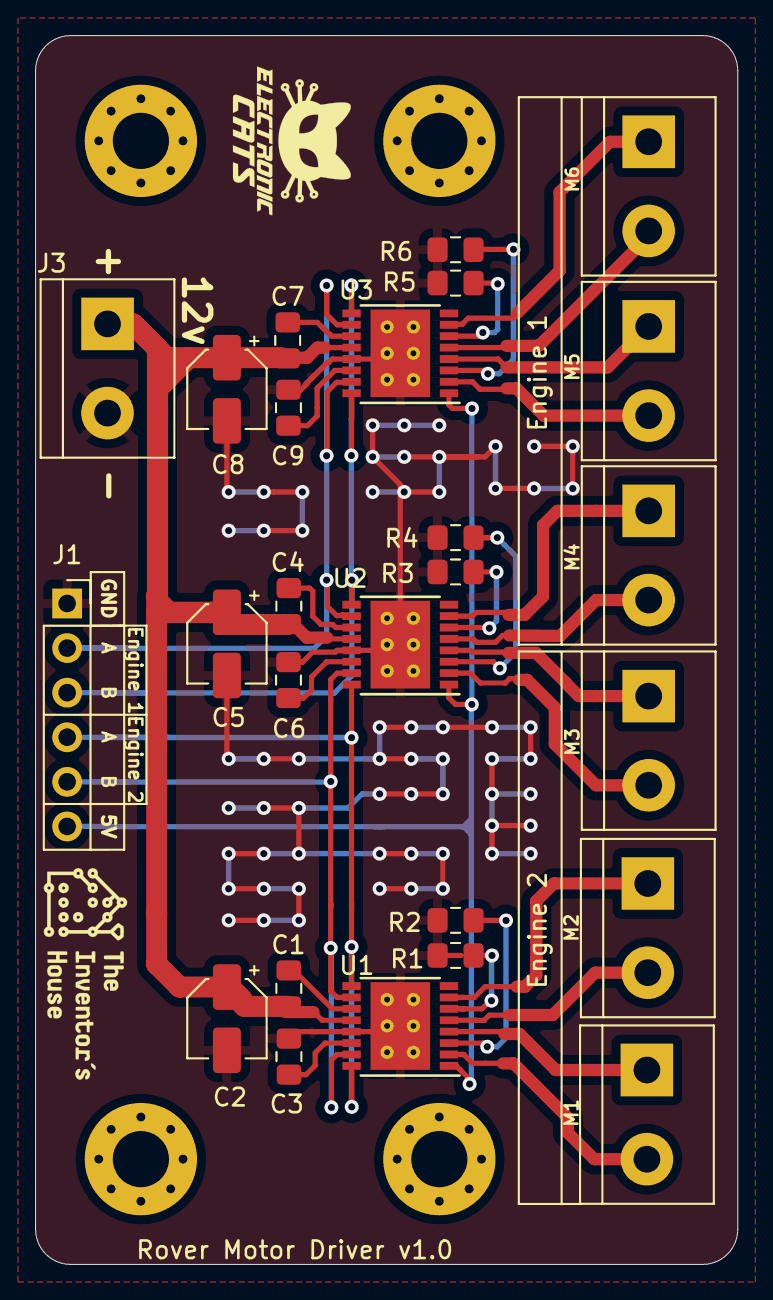
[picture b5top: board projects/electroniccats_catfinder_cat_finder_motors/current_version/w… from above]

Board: 2 copper layers, 40.0 x 70.0 mm, 26 parts (0 on the bottom side), 31 nets.

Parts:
C1, C4, C7: .01uF; C_0805_2012Metric_Pad1.15x1.40mm_HandSolder
C2, C5, C8: 10uF; CP_Elec_4x5.4
C3, C6, C9: 2.2uF; C_0805_2012Metric_Pad1.15x1.40mm_HandSolder
J1: Conn_01x06_Female; PinSocket_1x06_P2.54mm_Vertical
J3: Screw_Terminal_01x02; TerminalBlock_bornier-2_P5.08mm
M1, M2, M3, M4, M5, M6: Motor_DC; TerminalBlock_bornier-2_P5.08mm
R1, R2, R6: 200mOhms; R_0805_2012Metric_Pad1.15x1.40mm_HandSolder
R3, R4, R5: 200mOhm; R_0805_2012Metric_Pad1.15x1.40mm_HandSolder
U1, U2, U3: DRV8833PWP; HTSSOP-16-1EP_4.4x5mm_P0.65mm_EP3.4x5mm_Mask2.46x2.31mm_The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

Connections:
+12V: C1.1, C2.1, C4.1, C5.1, C7.1, C8.1, J3.1, U1.12, U2.12, U3.12
/ADER1: M5.2, U3.2
/ADER2: M5.1, U3.4
/AFDER1: M3.2, U2.2
/AFDER2: M3.1, U2.4
/AOUT1: M1.2, U1.2
/AOUT2: M1.1, U1.4
/BDER1: M6.1, U3.7
/BDER2: M6.2, U3.5
/BFDER1: M4.1, U2.7
/BFDER2: M4.2, U2.5
/BOUT1: M2.1, U1.7
/BOUT2: M2.2, U1.5
/GPIO4: J1.4, U1.9, U1.16, U2.16
/GPIO12: J1.5, U1.10, U1.15, U2.15
/GPIO14: J1.3, U2.9, U3.9, U3.16
/GPIO15: J1.2, U2.10, U3.10, U3.15
GND: C2.2, C3.2, C5.2, C6.2, C8.2, C9.2, J1.1, J3.2, R1.2, R2.2, R3.2, R4.2, R5.2, R6.2, U1.13, U1.17, U2.13, U2.17, U3.13, U3.17
unnamed: C1.2, U1.11
unnamed: C3.1, U1.14
unnamed: C4.2, U2.11
unnamed: C6.1, U2.14
unnamed: C7.2, U3.11
unnamed: C9.1, U3.14
unnamed: R1.1, U1.6
unnamed: R2.1, U1.3
unnamed: R3.1, U2.6
unnamed: R4.1, U2.3
unnamed: R5.1, U3.6
unnamed: R6.1, U3.3
VCC: J1.6, U1.1, U2.1, U3.1

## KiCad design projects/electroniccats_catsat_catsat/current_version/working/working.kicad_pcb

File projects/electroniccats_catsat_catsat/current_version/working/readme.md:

# catsat
 
## summary 
* id: electroniccats_catsat_catsat
* user: electroniccats
* name: catsat
* board: catsat
* repo: https://github.com/ElectronicCats/CatSat
* src_file_repo_kicad_pcb: OldVersion/CatSat.kicad_pcb
* src_file_repo_kicad_pcb_link: https://github.com/ElectronicCats/CatSat/tree/master/OldVersion/CatSat.kicad_pcb

* src_file_repo_sch: OldVersion/CatSat.sch
* src_file_repo_sch_link: https://github.com/ElectronicCats/CatSat/tree/master/OldVersion/CatSat.sch
* full details link: https://github.com/oomlout/oomlout_oomp_project_bot_v_2/tree/main/projects/electroniccats_catsat_catsat/current_version/working

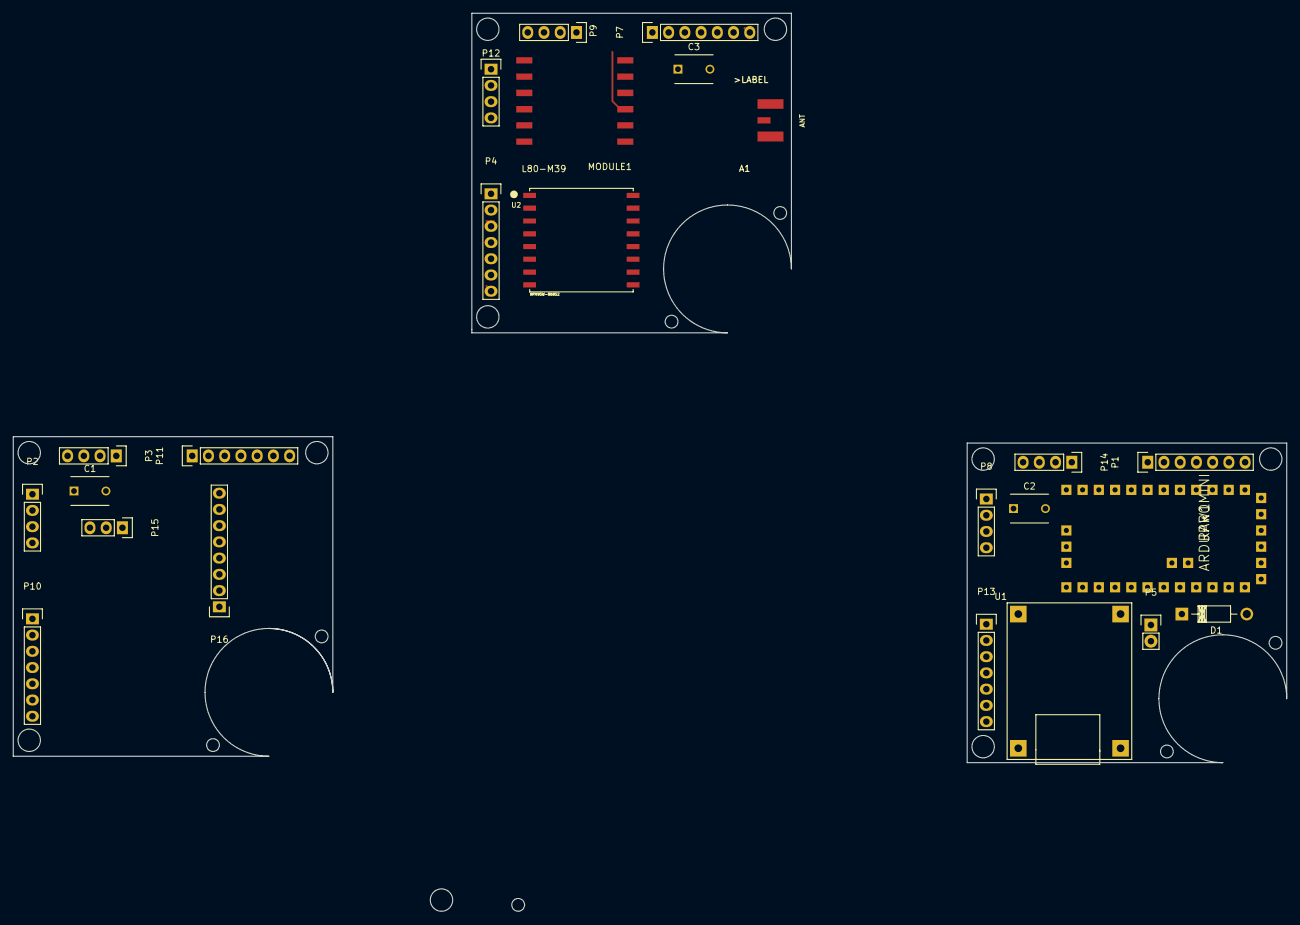
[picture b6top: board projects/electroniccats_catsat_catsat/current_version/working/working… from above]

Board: 2 copper layers, 199.2 x 140.5 mm, 24 parts (0 on the bottom side), 23 nets.

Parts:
A1: ANT; SMA_Conn_Ant
C1, C2, C3: C; C_Disc_D6_P5
D1: D; Diode_DO-41_SOD81_Horizontal_RM10
MODULE1: L80-M39; L80
P1, P4, P7, P10, P11, P13: CONN_01X07; Pin_Header_Straight_1x07
P2, P3, P8, P9, P12, P14: CONN_01X04; Pin_Header_Straight_1x04
P5: BATTERY; Pin_Header_Straight_1x02
P15: DHT22; Pin_Header_Straight_1x03
P16: GY-87; Pin_Header_Straight_1x08
RAW1: ARDUPROMINI; arduinoMiniPro
U1: 4056_CARG; 4056_lipoCharg
U2: RFM95W-868S2; RFM

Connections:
+BATT: C1.1, C2.1, C3.1, D1.1, MODULE1.4, P1.2, P4.1, P7.2, P10.1, P11.2, P13.1, P15.2, P16.1, RAW1.22, U2.13
A0: P2.4, P8.4, P12.4, RAW1.26
A1: P2.3, P8.3, P12.3, RAW1.25
A2: P2.2, P8.2, P12.2, RAW1.24
A3: P2.1, P8.1, P12.1, RAW1.23
D7: P3.3, P9.3, P14.3, RAW1.16
D8: P3.4, P9.4, P14.4, RAW1.17
DHT/D6: P1.7, P7.7, P11.7, P15.1, RAW1.15
GND: A1.1, A1.3, C1.2, C2.2, C3.2, MODULE1.3, MODULE1.12, P1.1, P4.2, P7.1, P10.2, P11.1, P13.2, P15.3, P16.2, RAW1.10, RAW1.20, U2.1, U2.8, U2.10
INT0: P3.1, P9.1, P14.1, RAW1.11, U2.14
INT1: P3.2, P9.2, P14.2, RAW1.12
MISO: P4.4, P10.4, P13.4, RAW1.28, U2.2
MOSI: P4.5, P10.5, P13.5, RAW1.29, U2.3
NSS: P4.6, P10.6, P13.6, RAW1.30, U2.5
unnamed: A1.2, U2.9
unnamed: D1.2, P5.1, U1.3
unnamed: P5.2, U1.4
RST: P4.7, P10.7, P13.7, RAW1.18, U2.6
SCK: P4.3, P10.3, P13.3, RAW1.27, U2.4
SCL: P1.3, P7.3, P11.3, P16.4, RAW1.32
SDA: P1.4, P7.4, P11.4, P16.5, RAW1.31
S_RX: MODULE1.2, P1.5, P7.5, P11.5, RAW1.14
S_TX: MODULE1.1, P1.6, P7.6, P11.6, RAW1.13
